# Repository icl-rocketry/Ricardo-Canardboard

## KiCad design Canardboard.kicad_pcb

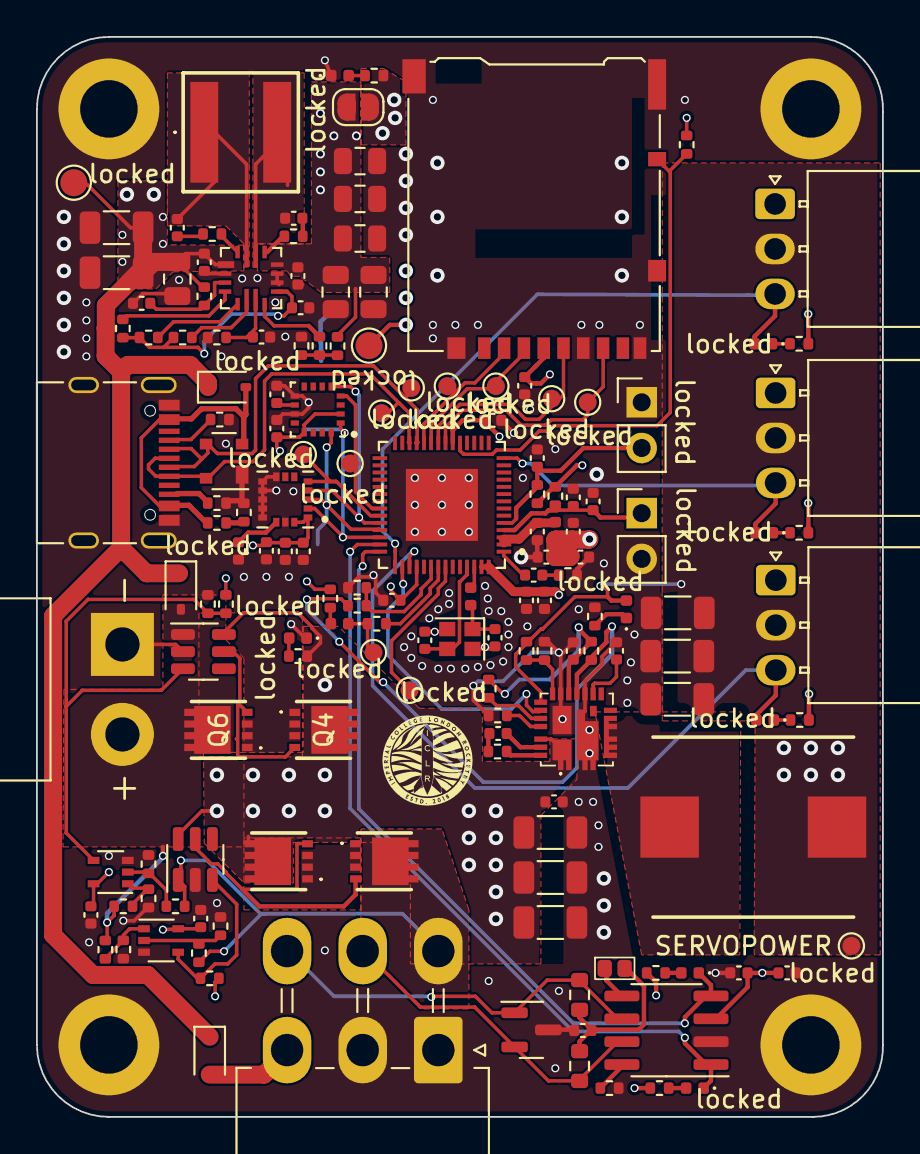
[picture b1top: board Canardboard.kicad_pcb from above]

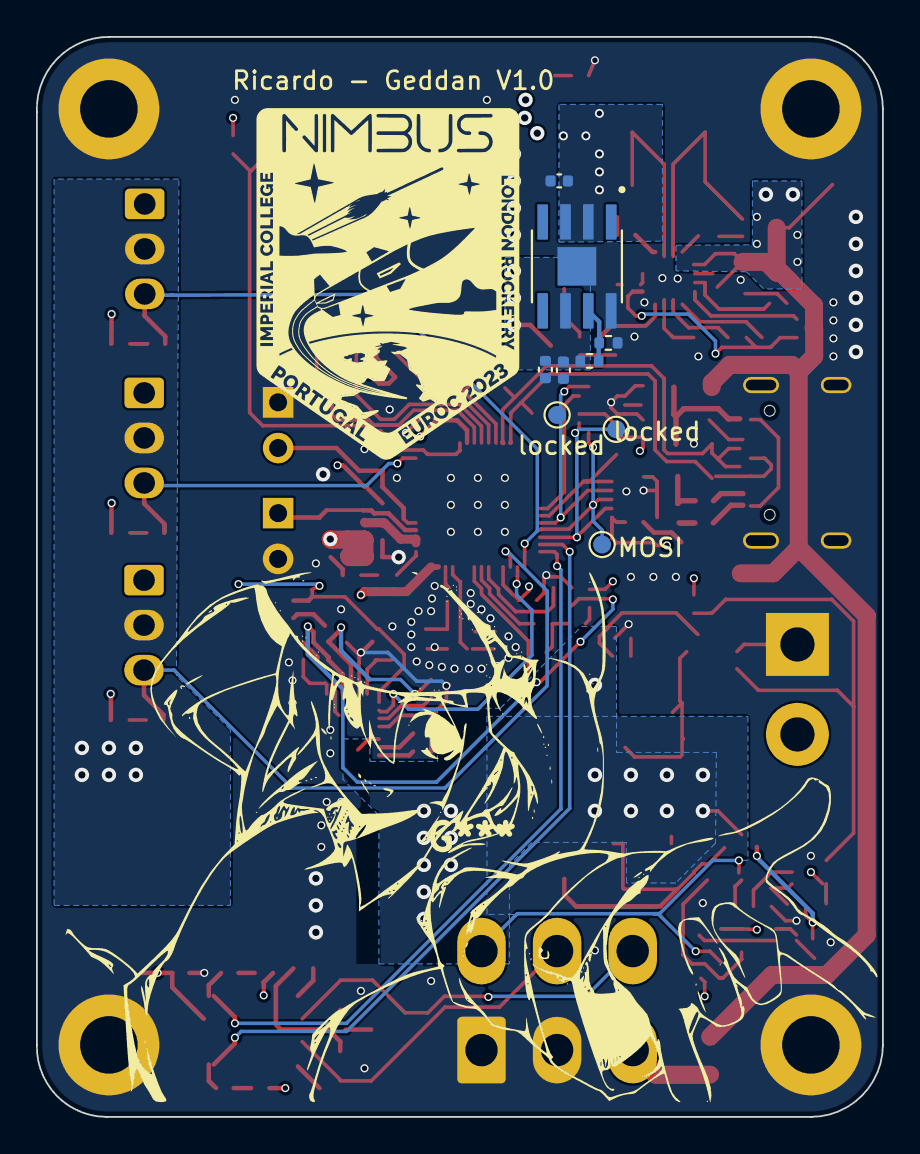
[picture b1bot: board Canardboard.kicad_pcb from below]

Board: 4 copper layers, 47.0 x 60.0 mm, 171 parts (9 on the bottom side), 94 nets.

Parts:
C1, C16, C29: 10uF; C_0402_1005Metric
C2, C4, C7, C20, C22, C23, C32, C42, C52: 1uF; C_0402_1005Metric
C3, C5, C6, C8, C10, C11, C26, C33, C44: 0.1uF; C_0402_1005Metric
C9, C31: 10nF; C_0402_1005Metric
C12: 4.2pF; C_0402_1005Metric
C13, C14: C; C_0402_1005Metric
C15, C40, C41, C49, C53, C54: 100nF; C_0402_1005Metric
C17: 47nF; C_0402_1005Metric
C18, C19, C35, C36, C37, C39, C45, C46: 47uF; C_1206_3216Metric
C21: 4.7uF; C_0402_1005Metric
C24, C25: DNP; C_0402_1005Metric
C30: 0.47uF; C_0402_1005Metric
C34: 2.2uF; C_0402_1005Metric
C43, C50, C51, C56, C57, C58: 22uF; C_0805_2012Metric
C48, C55: 22nF; C_0402_1005Metric
D1: SM712_SOT23; SOT-23
D2: SP0503BAHT; SOT-143
D3, D4, D5: D_Schottky; D_SOD-323
H1, H2, H3, H4: MountingHole_Pad; MountingHole_3.2mm_M3_DIN965_Pad
IC1: SIC437DED-T1-GE3; SiC437BEDT1GE3
J1: RBUS; Molex_Mini-Fit_Jr_5569-06A2_2x03_P4.20mm_Horizontal
J2: USB_C_Receptacle_USB2.0; USB_C_Receptacle_Palconn_UTC16-G
J3: Micro_SD_Card_Det; microSD_HC_Hirose_DM3AT-SF-PEJM5
J4: Conn_01x02_Male; AMASS_XT30PW-M_1x02_P2.50mm_Horizontal
J5, J6, J7: Conn_01x03_Male; Molex_Nano-Fit_105313-xx03_1x03_P2.50mm_Horizontal
JP1: TermJP; SmallerSolderJP
JP2: TermJP; SolderJumper-2_P1.3mm_Open_RoundedPad1.0x1.5mm
L1: 2.0nH; L_0402_1005Metric
L2: 20nH; L_0402_1005Metric
L4: 2.1uH; INDPM112100X400N
L5: 4.7uH; MPLAL60504R7
MOSI: TestPoint; TestPoint_Pad_D1.0mm
Q1, Q2, Q4, Q6: PXP012-30QLJ; PXP01230QLJ
R1, R3: 10K; R_0402_1005Metric
R2, R4, R13, R15, R42, R44, R46: 470; R_0402_1005Metric
R5: 47.5; R_0402_1005Metric
R6: 499; R_0402_1005Metric
R7, R22: 3k; R_0402_1005Metric
R8, R36, R37, R49: 0; R_0402_1005Metric
R9, R10: 60; R_0603_1608Metric
R11, R12: 5.1k; R_0402_1005Metric
R14, R18, R39, R40, R41: 10k; R_0402_1005Metric
R16, R23, R26, R27, R28, R29, R30, R31, R43, R45: 1k; R_0402_1005Metric
R17: 34k; R_0402_1005Metric
R19, R35, R47, R48: 100k; R_0402_1005Metric
R20: 200k; R_0402_1005Metric
R21: 2.2; R_0402_1005Metric
R24: 1.5k; R_0402_1005Metric
R25: 2.2k; R_0402_1005Metric
R32: 499k; R_0402_1005Metric
R33: 806k; R_0402_1005Metric
R34: 230k; R_0402_1005Metric
R38: 21.5k; R_0402_1005Metric
R50, R51: DNP; R_0402_1005Metric
SERVOPOWER: TestPoint; TestPoint_Pad_D1.0mm
U1: ESP32-S3; QFN40P700X700X90-57N
U2: SN65HVD230; SOIC-8_3.9x4.9mm_P1.27mm
U3, U4: LTC4412xS6; TSOT-23-6
U5: 74AHC1G00; SOT-353_SC-70-5
U6: 74AHC1G08; SOT-353_SC-70-5
U9: SC4215; SOIC127P599X175-9N
U10: MP28167GQ-A-Z
USBLED1: USB_LED; R_0402_1005Metric
Y1: 40MHz±10ppm; Crystal_SMD_2016-4Pin_2.0x1.6mm
locked: SERVOLED; LED_0402_1005Metric
locked#2, locked#6, locked#7, locked#10, locked#11, locked#15, locked#17, locked#18, locked#21, locked#25, locked#26, locked#27: TestPoint; TestPoint_Pad_D1.0mm
locked#3, locked#24: Conn_01x02_Male; PinHeader_1x02_P2.54mm_Vertical
locked#4: TX_LED; LED_0402_1005Metric
locked#5, locked#16: TestPoint; TestPoint_Pad_D1.5mm
locked#8, locked#19: SERVOLED; LED_0402_1005Metric
locked#9: CANRXLED; LED_0402_1005Metric
locked#12: MMC5983MA; PQFN50P300X300X100-16N
locked#13: ICM-20608-G; PQFN50P300X300X80-16N
locked#14: 3V3LED; LED_0402_1005Metric
locked#20: 12V_LED; LED_0402_1005Metric
locked#22: SERVOPWR_LED; LED_0402_1005Metric
locked#23: CANTXLED; LED_0402_1005Metric

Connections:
+3.3V: C1.1, C4.1, C5.1, C7.1, C9.1, C10.1, C11.1, C15.1, C16.1, C20.2, C22.2, C23.2, C25.2, C26.2, C31.1, C32.1, C33.1, C34.1, J3.4 (VDD), JP2.2 (B), L1.1, R1.1, R2.1, R3.1, R4.2, R14.1, R26.1, R27.1, R47.1, R48.1, R50.1, U1.20 (VDD3P3_RTC), U1.46 (VDD3P3_CPU), U1.55 (VDDA), U1.56 (VDDA), U2.3 (VCC), U5.5 (VCC), U6.5 (VCC), U9.6 (VOUT), locked#12.2 (VDD), locked#12.13 (VDDIO), locked#13.1 (VDDIO), locked#13.16 (VDD), locked#16.1
+12V: C39.2, C40.2, C45.2, C46.2, IC1.1 (VIN_1), IC1.2 (VIN_2), IC1.22 (VIN_3), IC1.26 (VIN_4), Q1.5 (D_1), Q1.6 (D_2), Q1.7 (D_3), Q1.8 (D_4), Q1.9 (D_5), Q4.5 (D_1), Q4.6 (D_2), Q4.7 (D_3), Q4.8 (D_4), Q4.9 (D_5), R7.1, U3.6 (SENSE), U4.6 (SENSE)
/BOOT: C8.1, R3.2, U1.5 (GPIO0/BOOT), locked#3.2
/BuckPGOOD: R24.2, R25.1, U1.48 (MTMS/JTAG/GPIO42)
/CAN+: D1.2 (A2), J1.5, R9.1, U2.7 (CANH)
/CAN-: D1.1 (A1), J1.6, R10.2, U2.6 (CANL)
/CAN-BUS/Vref: JP1.1 (A), U2.5 (Vref)
/CAN_RX: U1.42 (GPIO37), U2.4 (R), locked#9.1 (K)
/CAN_TX: U1.41 (GPIO36), U2.1 (D), locked#23.1 (K)
/CHIP_PU: C2.1, C3.1, R1.2, U1.4 (CHIP_PU/RESET), locked#24.1
/Data+: D2.4 (K), J2.A6 (D+), J2.B6 (D+), U1.26 (GPIO20/USB_D+/ADC2_CH9), locked#11.1
/Data-: D2.3 (K), J2.A7 (D-), J2.B7 (D-), U1.25 (GPIO19/USB_D-/ADC2_CH8), locked#25.1
/IMU_CS: U1.37 (SPICLK_P/GPIO47), locked#13.5 (CS), locked#18.1
/MAG_CS: U1.36 (SPICLK_N/GPIO48), locked#10.1, locked#12.4 (~SPI_CS)
/RXD: U1.50 (U0RXD/PROG/GPIO44), locked#7.1
/SD_CLK: J3.5 (CLK), U1.22 (GPIO16/ADC2_CH5/XTAL_32K_N), locked#6.1
/SD_CS: J3.2 (DAT3/CD), U1.24 (GPIO18/ADC2_CH7/DAC_1), locked#2.1
/SD_DET: J3.10 (DET_A), R14.2, U1.19 (GPIO14/ADC2_CH3)
/SD_MISO: J3.7 (DAT0), U1.21 (GPIO15/ADC2_CH4/XTAL_32K_P), locked#17.1
/SD_MOSI: J3.3 (CMD), U1.23 (GPIO17/ADC2_CH6/DAC_2), locked#21.1
/SERVOBUCK_EN: IC1.19 (EN), U1.44 (MTCK/JTAG/GPIO39)
/SERVO_PWR: C35.1, C36.1, C37.1, IC1.18 (VOUT), J5.2, J6.2, J7.2, L4.1, R17.2, SERVOPOWER.1, locked#22.2 (A)
/SERVO_SGNL1: J5.3, U1.43 (GPIO38), locked.2 (A)
/SERVO_SGNL2: J6.3, U1.14 (GPIO9/ADC1_CH8), locked#19.2 (A)
/SERVO_SGNL3: J7.3, U1.45 (MTDO/JTAG/GPIO40), locked#8.2 (A)
/SPI_CLK: U1.40 (GPIO35), locked#12.1 (SCL/SPI_SCK), locked#13.2 (SCL/SCLK), locked#26.1
/SPI_MISO: U1.38 (GPIO33), locked#12.5 (SPI_SDO), locked#13.4 (AD0/SDO), locked#27.1
/SPI_MOSI: MOSI.1, U1.39 (GPIO34), locked#12.16 (SDA/SPI_SDI), locked#13.3 (SDA/SDI)
/TXD: R6.1, locked#4.1 (K), locked#15.1
/rbusmosfets/BatteryPower: D3.2 (A), J4.2, Q6.5 (D_1), Q6.6 (D_2), Q6.7 (D_3), Q6.8 (D_4), Q6.9 (D_5), R16.1, R43.1, U4.1 (VIN)
/rbusmosfets/RBUS_3.3: D4.2 (A), J1.3
/rbusmosfets/RBUS_DEPL: J1.4, Q2.5 (D_1), Q2.6 (D_2), Q2.7 (D_3), Q2.8 (D_4), Q2.9 (D_5), R23.2, R45.2, U3.1 (VIN)
/servopower/PGOOD: IC1.14 (PGOOD), R18.1, R24.1
/servopower/SW: IC1.5 (SW_1), IC1.6 (SW_2), IC1.7 (SW_3), IC1.8 (SW_4), IC1.9 (SW_5), IC1.30 (SW_6), L4.2
/servopower/VDD: C42.1, IC1.15 (VDD), R18.2, R20.2
/servopower/uC_VCC: C52.1, R39.1, R40.1, R41.1, U10.9 (VCC)
/servopower/uC_VOUT: C24.1, C49.1, C50.1, C51.1, C56.1, C57.1, C58.1, JP2.1 (A), R34.1, U9.2 (EN), U9.3 (VIN), U10.12 (OUT)
GND: C1.2, C2.2, C3.2, C4.2, C5.2, C6.2, C7.2, C8.2, C9.2, C10.2, C11.2, C13.2, C14.2, C15.2, C16.2, C17.2, C18.2, C19.2, C20.1, C21.1, C22.1, C23.1, C24.2, C25.1, C26.1, C29.2, C30.2, C31.2, C32.2, C33.2, C34.2, C35.2, C36.2, C37.2, C39.1, C40.1, C41.2, C42.2, C43.2, C45.1, C46.1, C48.1, C49.2, C50.2, C51.2, C52.2, C55.2, C56.2, C57.2, C58.2, D1.3 (common), D2.1 (A), H1.1, H2.1, H3.1, H4.1, IC1.3 (PGND__1), IC1.4 (PGND__2), IC1.13 (PGND__3), IC1.16 (AGND_1), IC1.25 (AGND_2), IC1.27 (PGND__4), IC1.29 (PGND__5), J1.1, J1.2, J2.A1 (GND), J2.A12 (GND), J2.B1 (GND), J2.B12 (GND), J2.S1 (SHIELD), J3.6 (VSS), J3.9 (DET_B), J3.11 (SHIELD), J4.1, J5.1, J6.1, J7.1, R5.1, R8.2, R11.2, R12.1, R15.2, R19.2, R22.2, R25.2, R28.1, R29.1, R30.1, R31.1, R35.2, R38.1, R42.2, R44.2, R46.2, R49.2, R51.2, U1.57 (GND), U2.2 (GND), U3.2 (GND), U4.2 (GND), U5.3 (GND), U6.3 (GND), U9.8 (GND), U9.9 (GND), U10.2 (GND), U10.10 (AGND), U10.11 (GND), USBLED1.1 (K), Y1.2, Y1.4, locked#3.1, locked#12.9 (GND), locked#12.11 (GND), locked#13.8 (FSYNC), locked#13.9 (GND), locked#13.10 (GND), locked#13.11 (GND), locked#13.12 (GND), locked#13.13 (GND), locked#13.15 (GND), locked#14.1 (K), locked#20.1 (K), locked#24.2
unnamed: R4.1, locked#14.2 (A)
unnamed: R7.2, locked#20.2 (A)
unnamed: C6.1, L1.2, U1.2 (VDD3P3), U1.3 (VDD3P3)
unnamed: C12.1, R5.2
unnamed: C14.1, L2.2, Y1.1
unnamed: C44.1, R21.1
unnamed: C53.1, R36.2
unnamed: C54.1, R37.2
unnamed: R27.2, locked#9.2 (A)
unnamed: R26.2, locked#23.2 (A)
unnamed: C44.2, IC1.23 (BOOT)
unnamed: IC1.17 (FB), R17.1, R22.1
unnamed: IC1.21 (MODE1), R19.1
unnamed: IC1.20 (MODE2), R20.1
unnamed: IC1.24 (PHASE), R21.2
unnamed: C21.2, IC1.12 (VDRV)
unnamed: J2.A5 (CC1), R11.1
unnamed: J2.B5 (CC2), R12.2
unnamed: C17.1, JP1.2 (B), R9.2, R10.1
unnamed: Q1.4 (G), Q2.4 (G), U3.5 (GATE)
unnamed: Q1.1 (S_1), Q1.2 (S_2), Q1.3 (S_3), Q2.1 (S_1), Q2.2 (S_2), Q2.3 (S_3)
unnamed: Q4.4 (G), Q6.4 (G), U4.5 (GATE)
unnamed: Q4.1 (S_1), Q4.2 (S_2), Q4.3 (S_3), Q6.1 (S_1), Q6.2 (S_2), Q6.3 (S_3)
unnamed: R15.1, R16.2, U5.1
unnamed: R23.1, R42.1, U5.2
unnamed: R33.1, R34.2, R35.1
unnamed: R43.2, R44.1, U6.1
unnamed: R45.1, R46.1, U6.2
unnamed: R28.2, locked.1 (K)
unnamed: R29.2, locked#19.1 (K)
unnamed: R30.2, locked#8.1 (K)
unnamed: R31.2, locked#22.1 (K)
unnamed: R2.2, locked#4.2 (A)
unnamed: C12.2, U1.1 (LNA_IN/RF)
unnamed: R6.2, U1.49 (U0TXD/PROG/GPIO43)
unnamed: C13.1, U1.53 (XTAL_N), Y1.3
unnamed: L2.1, U1.54 (XTAL_P)
unnamed: R8.1, U2.8 (Rs)
unnamed: R47.2, U3.3 (CTL), U6.4
unnamed: R48.2, R49.1, U4.3 (CTL), U5.4
unnamed: C30.1, locked#13.14 (REGOUT)
unnamed: C29.1, locked#12.10 (CAP)
unnamed: R50.2, R51.1, U9.7 (ADJ)
unnamed: R39.2, U10.4 (ALT)
unnamed: R37.1, U10.16 (BST1)
unnamed: R36.1, U10.13 (BST2)
unnamed: C48.2, R32.2, U10.3 (EN)
unnamed: R33.2, U10.8 (FB)
unnamed: C55.1, R38.2, U10.7 (OC)
unnamed: R40.2, U10.5 (SCL)
unnamed: R41.2, U10.6 (SDA)
unnamed: C54.2, L5.1, U10.15 (SW1)
unnamed: C53.2, L5.2, U10.14 (SW2)
unnamed: R13.2, USBLED1.2 (A)
RBUS_uC_V: C18.1, C19.1, C41.1, C43.1, D3.1 (K), D4.1 (K), D5.1 (K), R32.1, U10.1 (IN), locked#5.1
VBUS: D2.2 (K), D5.2 (A), J2.A4 (VBUS), J2.A9 (VBUS), J2.B4 (VBUS), J2.B9 (VBUS), R13.1

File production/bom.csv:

Designator,Footprint,Quantity,Value,LCSC Part #
12V,402,1,12V_LED,
3V3_2,402,1,3V3LED,
"3V3, RuCV",TestPoint_Pad_D1.5mm,2,TestPoint,
"BOOT, EN",PinHeader_1x02_P2.54mm_Vertical,2,Conn_01x02_Male,
"C1, C16, C29",402,3,10uF,
"C10, C11, C26, C3, C33, C44, C5, C6, C8",402,9,0.1uF,
C12,402,1,4.2pF,
"C13, C14",402,2,11pF,
"C15, C40, C41, C49, C53, C54",402,6,100nF,
C17,402,1,47nF,
,,,,
"C35, C36, C37",1206,3,47uF,
"C2, C20, C22, C23, C32, C4, C42, C52, C7",402,9,1uF,
C21,402,1,4.7uF,
"C24, C25, R50, R51",402,4,DNP,
C30,402,1,0.47uF,
"C31, C9",402,2,10nF,
C34,402,1,2.2uF,
"C43, C50, C51, C56, C57, C58",805,6,22uF,
"C48, C55",402,2,22nF,
"CLK_2, CLK, CS, D+, D-, ICS, IO, MCS, MISO, MOSI, OI, RX, SERVOPOWER, TX",TestPoint_Pad_D1.0mm,14,TestPoint,
CRX,402,1,CANRXLED,
CTX,402,1,CANTXLED,
D1,SOT-23,1,SM712_SOT23,
D2,SOT-143,1,SP0503BAHT,
"D3, D4, D5",D_SOD-323,3,D_Schottky,
"H1, H2, H3, H4",MountingHole_3.2mm_M3_DIN965_Pad,4,MountingHole_Pad,
IC1,SiC437BEDT1GE3,1,SIC437AED-T1-GE3,
IMU,PQFN50P300X300X80-16N,1,ICM-20608-G,
J1,Molex_Mini-Fit_Jr_5569-06A2_2x03_P4.20mm_Horizontal,1,RBUS,
J2,USB_C_Receptacle_Palconn_UTC16-G,1,USB_C_Receptacle_USB2.0,
J3,microSD_HC_Hirose_DM3AT-SF-PEJM5,1,Micro_SD_Card_Det,
J4,AMASS_XT30PW-M_1x02_P2.50mm_Horizontal,1,Conn_01x02_Male,
"J5, J6, J7",Molex_Nano-Fit_105313-xx03_1x03_P2.50mm_Horizontal,3,Conn_01x03_Male,
JP1,SmallerSolderJP,1,TermJP,
JP2,SolderJumper-2_P1.3mm_Open_RoundedPad1.0x1.5mm,1,TermJP,
L1,402,1,2.0nH,
L2,402,1,20nH,
L4,INDPM112100X400N,1,2.1uH,
L5,MPLAL60504R7,1,4.7uH,
MAG,PQFN50P300X300X100-16N,1,MMC5983MA,
,,,,
"R1, R14, R18, R3, R39, R40, R41",402,7,10K,
"R10, R9",603,2,60,
"R11, R12",402,2,5.1k,
"R13, R15, R2, R4, R42, R44, R46",402,7,470,
"R16, R23, R26, R27, R28, R29, R30, R31, R43, R45",402,10,1k,
R17,402,1,34k,
"R19, R35, R47, R48",402,4,100k,
R20,402,1,200k,
R21,402,1,2.2,
"R22, R7",402,2,3k,
R24,402,1,1.5k,
R25,402,1,2.2k,
R32,402,1,499k,
R33,402,1,806k,
R34,402,1,230k,
"R36, R37, R49, R8",402,4,0,
R38,402,1,21.5k,
,,,,
R6,402,1,499,
"S1, S2, S3",402,3,SERVOLED,
SP,402,1,SERVOPWR_LED,
TXLED,402,1,TX_LED,
,,,,
U10,MP28167GQ-A-Z,1,MP28167GQ-A-Z,
U2,SOIC-8_3.9x4.9mm_P1.27mm,1,SN65HVD230,
"U3, U4",TSOT-23-6,2,LTC4412xS6,
U5,SOT-353_SC-70-5,1,74AHC1G00,
U6,SOT-353_SC-70-5,1,74AHC1G08,
,,,,
USBLED1,402,1,USB_LED,
Y1,Crystal_SMD_2016-4Pin_2.0x1.6mm,1,40MHz±10ppm,

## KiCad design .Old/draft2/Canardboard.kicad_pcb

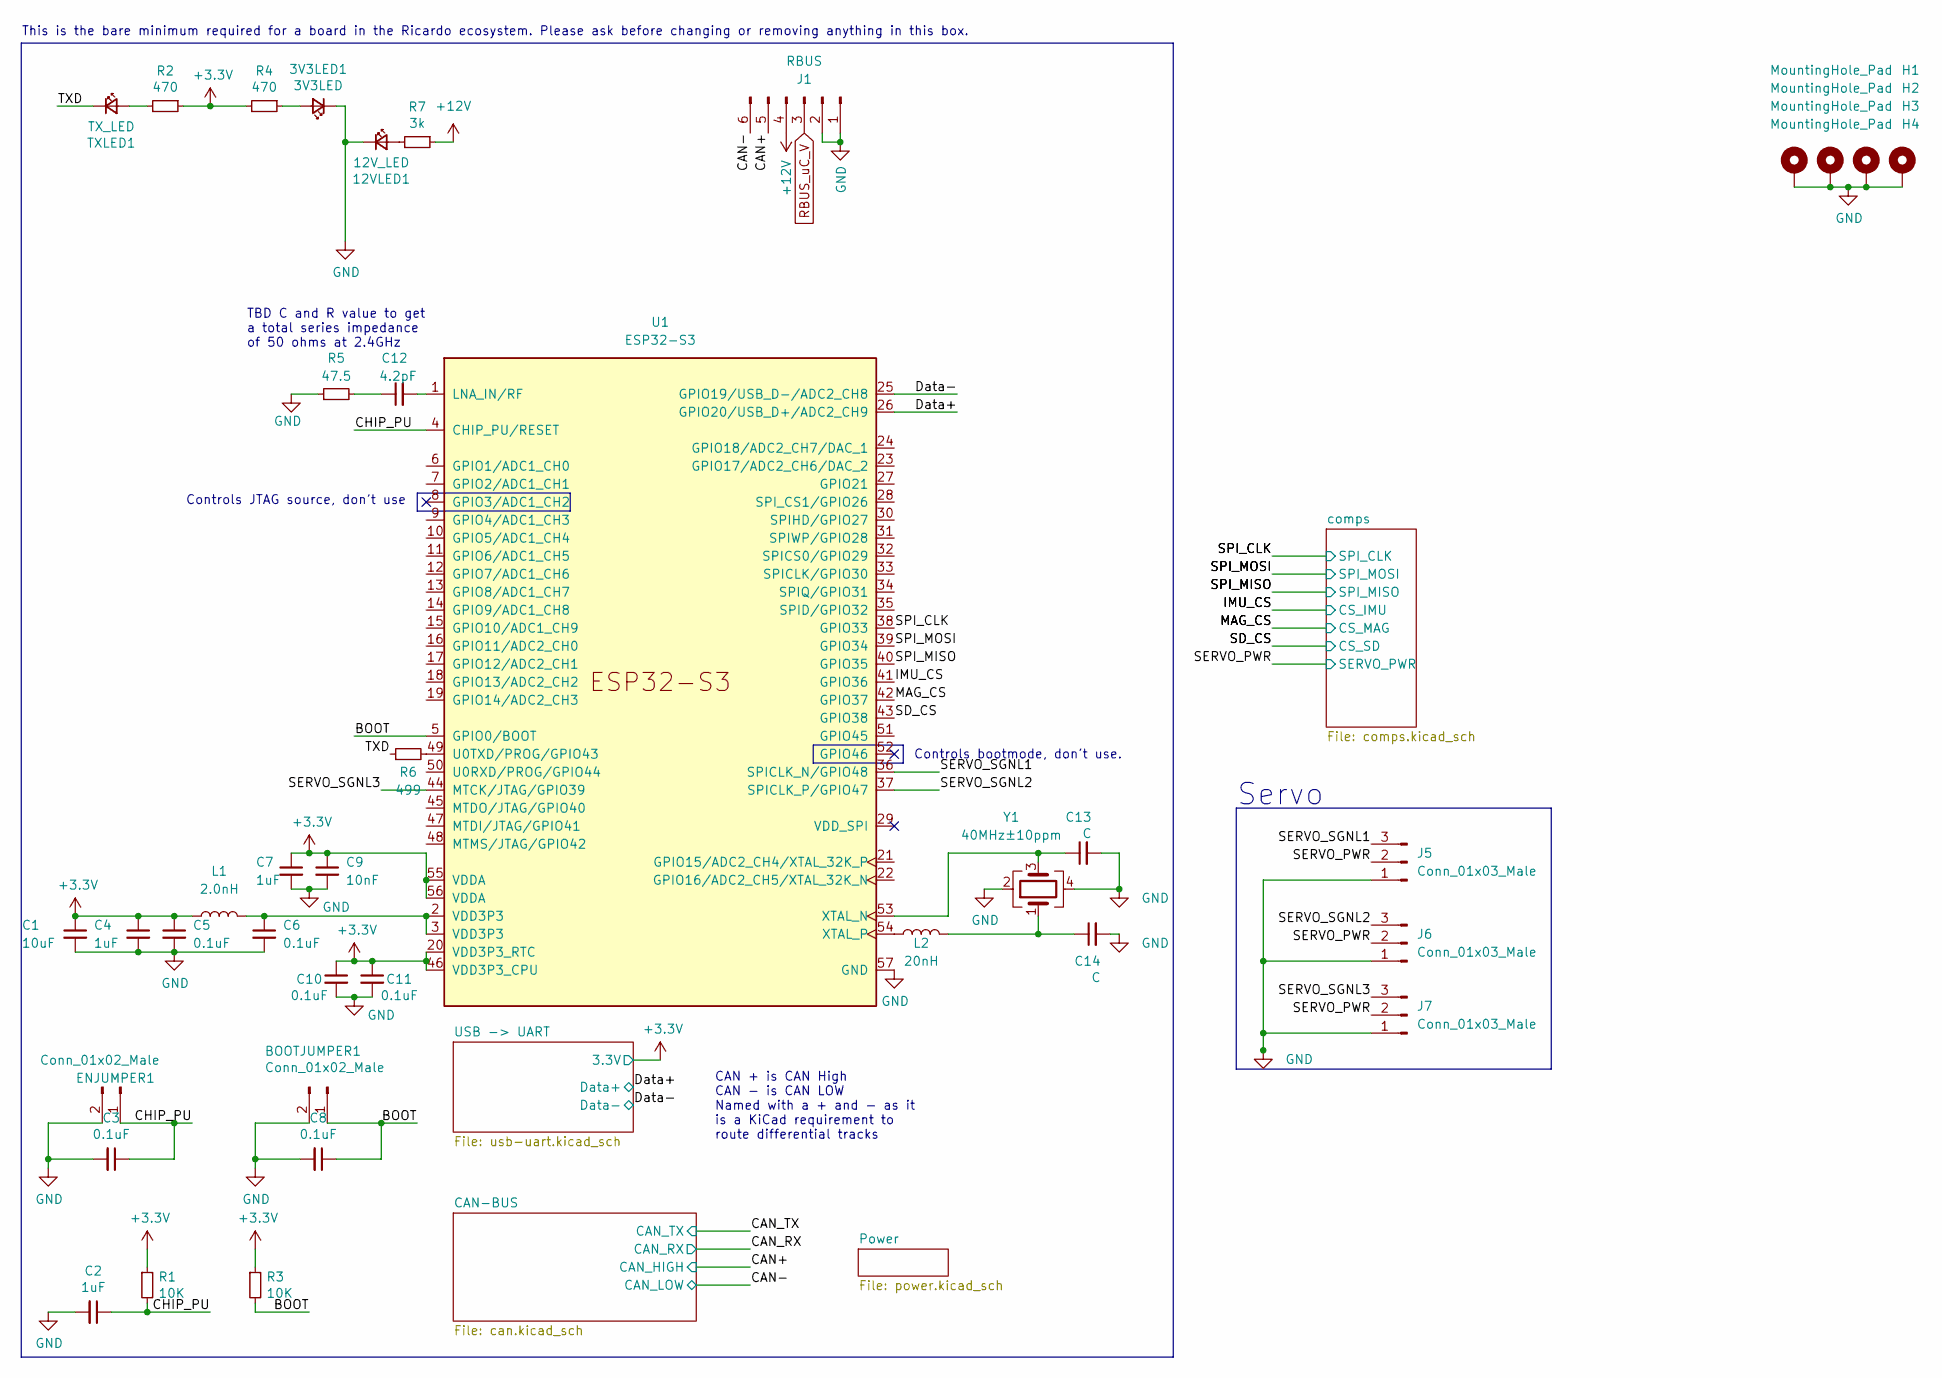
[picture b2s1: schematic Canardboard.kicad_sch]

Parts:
3V3LED1: 3V3LED; R_0402_1005Metric
12VLED1: 12V_LED; R_0402_1005Metric
BOOTJUMPER1: Conn_01x02_Male; PinHeader_1x02_P2.54mm_Vertical
C1: 10uF; C_0402_1005Metric
C2, C4, C7: 1uF; C_0402_1005Metric
C3, C5, C6, C8, C10, C11: 0.1uF; C_0402_1005Metric
C9: 10nF; C_0402_1005Metric
C12: 4.2pF; C_0402_1005Metric
C13, C14: C; C_0402_1005Metric
ENJUMPER1: Conn_01x02_Male; PinHeader_1x02_P2.54mm_Vertical
H1, H2, H3, H4: MountingHole_Pad; MountingHole_3.2mm_M3_DIN965_Pad
J1: RBUS; Molex_Mini-Fit_Jr_5566-06A_2x03_P4.20mm_Vertical
J5, J6, J7: Conn_01x03_Male; AMASS_MR30PW-M_1x03_P3.50mm_Horizontal
L1: 2.0nH; L_0402_1005Metric
L2: 20nH; L_0402_1005Metric
R1, R3: 10K; R_0402_1005Metric
R2, R4: 470; R_0402_1005Metric
R5: 47.5; R_0402_1005Metric
R6: 499; R_0402_1005Metric
R7: 3k; R_0402_1005Metric
TXLED1: TX_LED; R_0402_1005Metric
U1: ESP32-S3; QFN-56-1EP_7x7mm_P0.4mm_EP5.6x5.6mm
Y1: 40MHz±10ppm; Crystal_SMD_2016-4Pin_2.0x1.6mm

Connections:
+3V3: C1.1, C4.1, C5.1, C7.1, C9.1, C10.1, C11.1, L1.1, R1.1, R2.1, R3.1, R4.2, U1.20 (VDD3P3_RTC), U1.46 (VDD3P3_CPU), U1.55 (VDDA), U1.56 (VDDA); also elsewhere on the board
+12V: J1.4, R7.1; also elsewhere on the board
/BOOT: BOOTJUMPER1.1, C8.1, R3.2, U1.5 (GPIO0/BOOT)
/CAN+: J1.5; also elsewhere on the board
/CAN-: J1.6; also elsewhere on the board
/CHIP_PU: C2.1, C3.1, ENJUMPER1.1, R1.2, U1.4 (CHIP_PU/RESET)
/Data+: U1.26 (GPIO20/USB_D+/ADC2_CH9); also elsewhere on the board
/Data-: U1.25 (GPIO19/USB_D-/ADC2_CH8); also elsewhere on the board
/IMU_CS: U1.41 (GPIO36); also elsewhere on the board
/MAG_CS: U1.42 (GPIO37); also elsewhere on the board
/SD_CS: U1.43 (GPIO38); also elsewhere on the board
/SERVO_PWR: J5.2, J6.2, J7.2; also elsewhere on the board
/SERVO_SGNL1: J5.3, U1.36 (SPICLK_N/GPIO48)
/SERVO_SGNL2: J6.3, U1.37 (SPICLK_P/GPIO47)
/SERVO_SGNL3: J7.3, U1.44 (MTCK/JTAG/GPIO39)
/SPI_CLK: U1.38 (GPIO33); also elsewhere on the board
/SPI_MISO: U1.40 (GPIO35); also elsewhere on the board
/SPI_MOSI: U1.39 (GPIO34); also elsewhere on the board
/TXD: R6.1, TXLED1.1 (K)
unnamed: 3V3LED1.2 (A), R4.1
unnamed: 12VLED1.2 (A), R7.2
unnamed: C6.1, L1.2, U1.2 (VDD3P3), U1.3 (VDD3P3)
unnamed: C12.1, R5.2
unnamed: C14.1, L2.2, Y1.1
unnamed: R2.2, TXLED1.2 (A)
unnamed: C12.2, U1.1 (LNA_IN/RF)
unnamed: R6.2, U1.49 (U0TXD/PROG/GPIO43)
unnamed: C13.1, U1.53 (XTAL_N), Y1.3
unnamed: L2.1, U1.54 (XTAL_P)
RBUS_uC_V: J1.3; also elsewhere on the board

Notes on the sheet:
Controls bootmode, don't use.
This is the bare minimum required for a board in the Ricardo ecosystem. Please ask before changing or removing anything in this box.
TBD C and R value to get a total series impedance of 50 ohms at 2.4GHz
CAN + is CAN High CAN - is CAN LOW Named with a + and - as it is a KiCad requirement to route differential tracks
Controls JTAG source, don't use
Servo

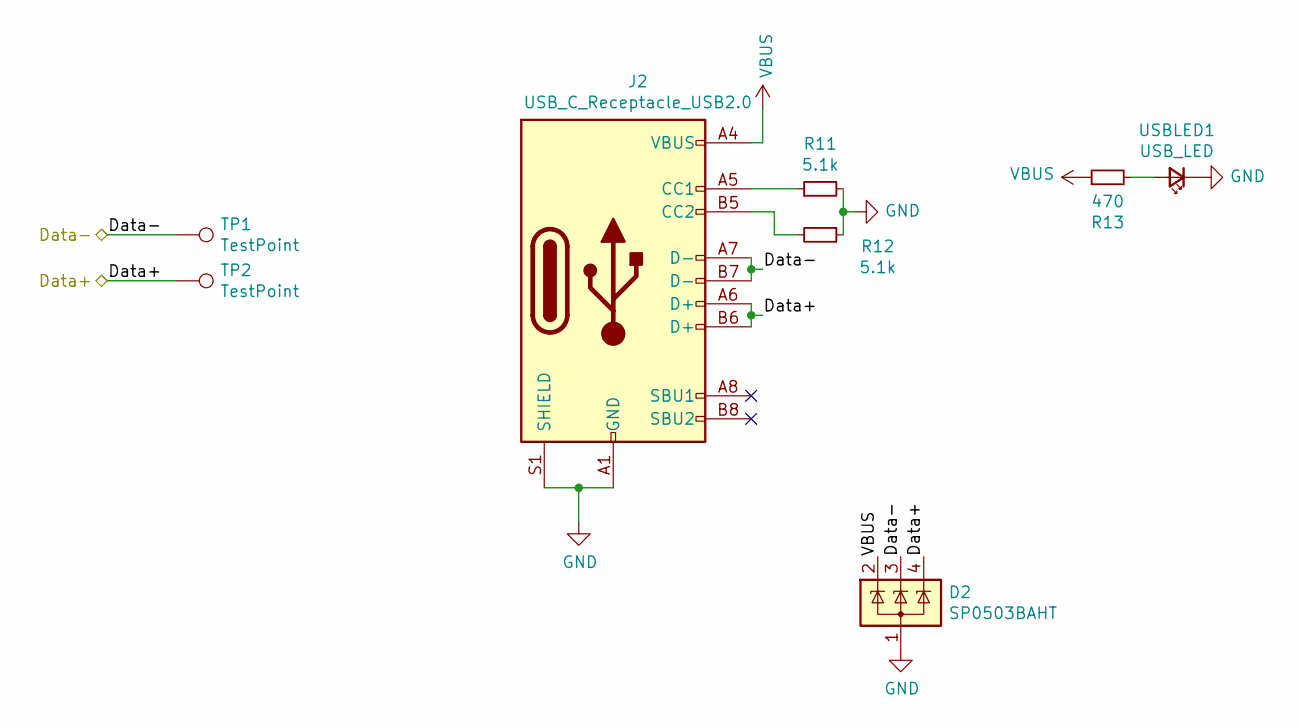
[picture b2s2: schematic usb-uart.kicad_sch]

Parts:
D2: SP0503BAHT; SOT-143
J2: USB_C_Receptacle_USB2.0; USB_C_Receptacle_Palconn_UTC16-G
R11, R12: 5.1k; R_0402_1005Metric
R13: 470; R_0402_1005Metric
TP1, TP2: TestPoint; TestPoint_Pad_D1.0mm
USBLED1: USB_LED; R_0402_1005Metric

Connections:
/Data+: D2.4 (K), J2.A6 (D+), J2.B6 (D+), TP2.1; also elsewhere on the board
/Data-: D2.3 (K), J2.A7 (D-), J2.B7 (D-), TP1.1; also elsewhere on the board
unnamed: J2.A5 (CC1), R11.1
unnamed: J2.B5 (CC2), R12.2
unnamed: R13.2, USBLED1.2 (A)
VBUS: D2.2 (K), J2.A4 (VBUS), J2.A9 (VBUS), J2.B4 (VBUS), J2.B9 (VBUS), R13.1; also elsewhere on the board

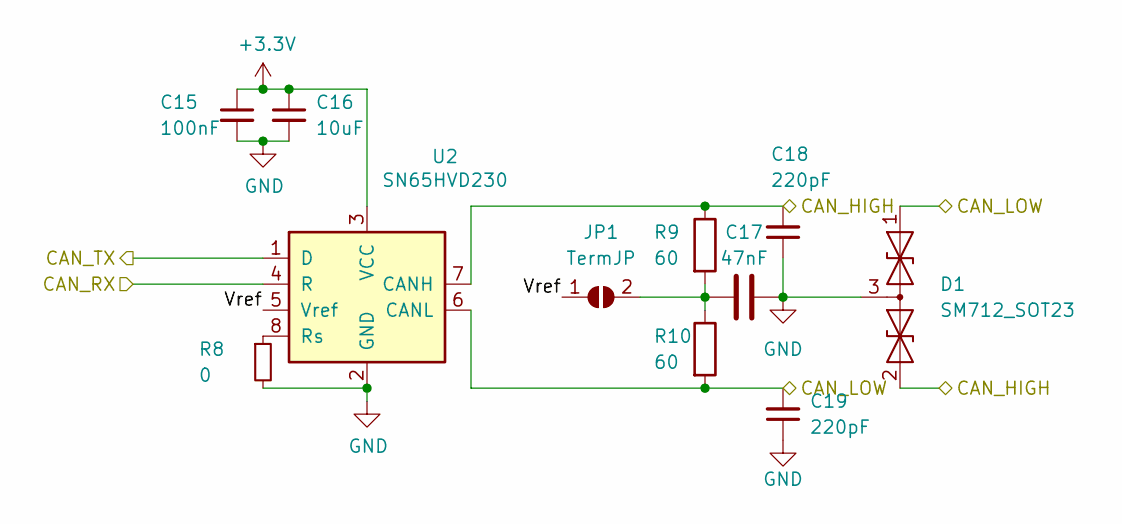
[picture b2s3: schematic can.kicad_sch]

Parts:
C15: 100nF; C_0402_1005Metric
C16: 10uF; C_0402_1005Metric
C17: 47nF; C_0402_1005Metric
C18, C19: 220pF; C_0402_1005Metric
D1: SM712_SOT23; SOT-23
JP1: TermJP; SolderJumper-2_P1.3mm_Open_RoundedPad1.0x1.5mm
R8: 0; R_0603_1608Metric
R9, R10: 60; R_0603_1608Metric
U2: SN65HVD230; SOIC-8_3.9x4.9mm_P1.27mm

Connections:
+3V3: C15.1, C16.1, U2.3 (VCC); also elsewhere on the board
/CAN+: C18.2, D1.2 (A2), R9.1, U2.7 (CANH); also elsewhere on the board
/CAN-: C19.2, D1.1 (A1), R10.2, U2.6 (CANL); also elsewhere on the board
/CAN-BUS/Vref: JP1.1 (A), U2.5 (Vref)
/CAN_RX: U2.4 (R)
/CAN_TX: U2.1 (D)
unnamed: C17.1, JP1.2 (B), R9.2, R10.1
unnamed: R8.1, U2.8 (Rs)

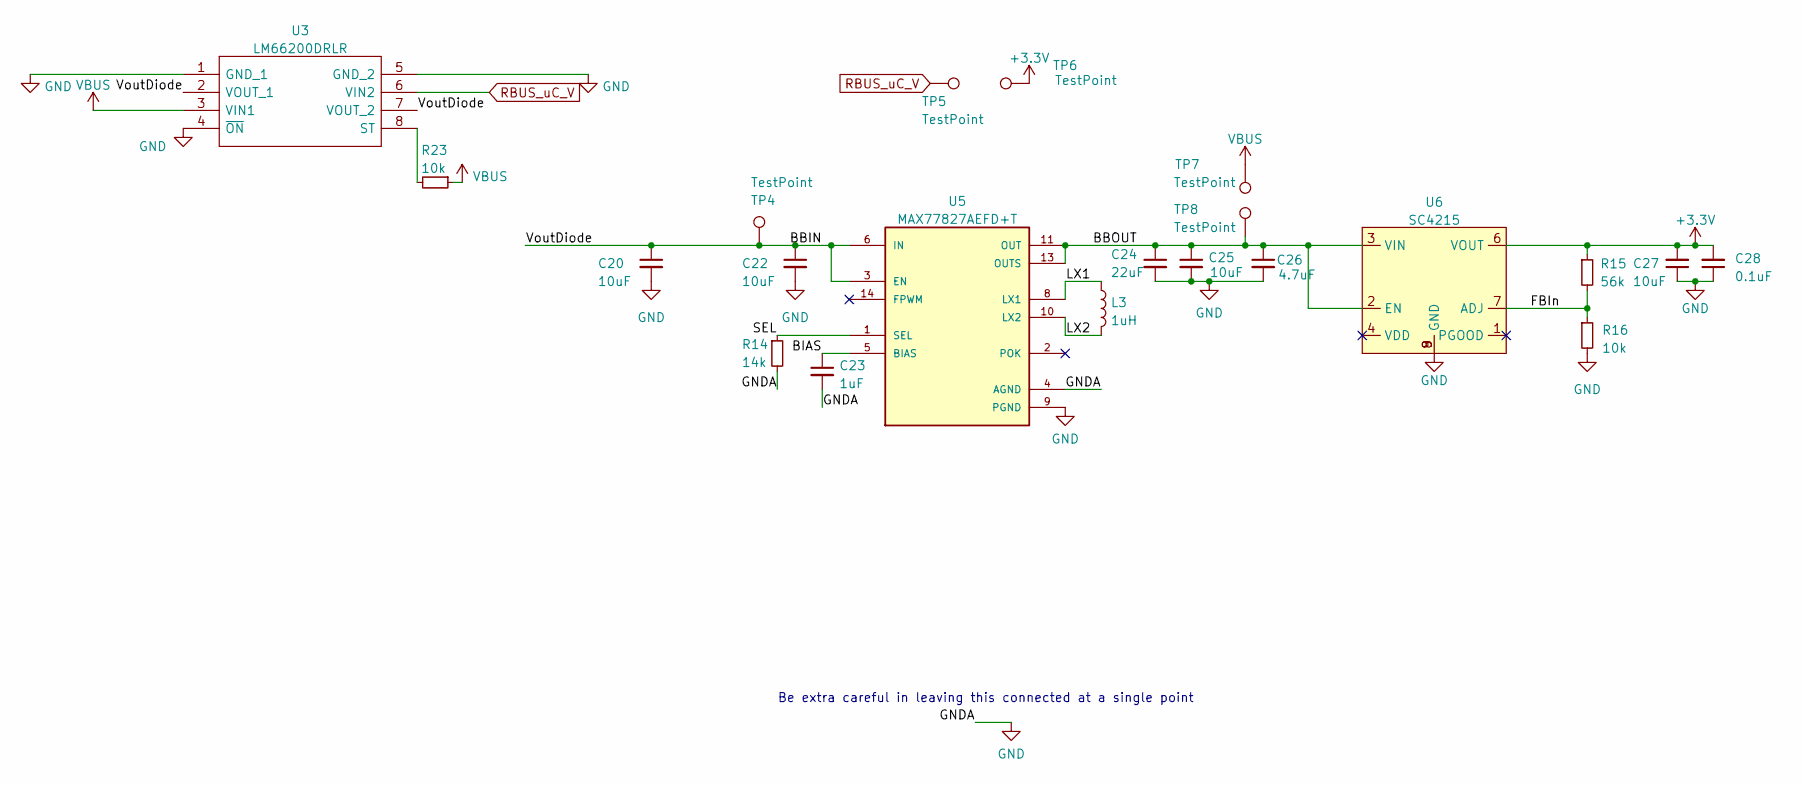
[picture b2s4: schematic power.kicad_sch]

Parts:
C20, C25, C27: 10uF; C_0402_1005Metric
C22: 10uF; C_0603_1608Metric
C23: 1uF; C_0402_1005Metric
C24: 22uF; C_0603_1608Metric
C26: 4.7uF; C_0402_1005Metric
C28: 0.1uF; C_0402_1005Metric
L3: 1uH; L_0805_2012Metric
R14: 14k; R_0402_1005Metric
R15: 56k; R_0402_1005Metric
R16, R23: 10k; R_0402_1005Metric
TP4, TP5, TP6, TP7, TP8: TestPoint; TestPoint_Pad_D1.5mm
U3: LM66200DRLR; SOTFL50P160X60-8N; Manufacturer_Part_Number LM66200DRLR; Mouser Part Number 595-LM66200DRLR
U5: MAX77827AEFD+T; CONV_MAX77827AEFD+T; PARTREV B
U6: SC4215; SOIC127P599X175-9N

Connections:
+3V3: C27.2, C28.2, R15.1, TP6.1, U6.6 (VOUT); also elsewhere on the board
/Power/BBIN: C20.1, C22.1, TP4.1, U3.2 (VOUT_1), U3.7 (VOUT_2), U5.3 (EN), U5.6 (IN)
/Power/BBOUT: C24.1, C25.1, C26.1, TP8.1, U5.11 (OUT), U5.13 (OUTS), U6.2 (EN), U6.3 (VIN)
/Power/BIAS: C23.1, U5.5 (BIAS)
/Power/FBIn: R15.2, R16.1, U6.7 (ADJ)
/Power/LX1: L3.1, U5.8 (LX1)
/Power/LX2: L3.2, U5.10 (LX2)
/Power/SEL: R14.1, U5.1 (SEL)
unnamed: R23.2, U3.8 (ST)
RBUS_uC_V: TP5.1, U3.6 (VIN2); also elsewhere on the board
VBUS: R23.1, TP7.1, U3.3 (VIN1); also elsewhere on the board

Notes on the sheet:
Be extra careful in leaving this connected at a single point

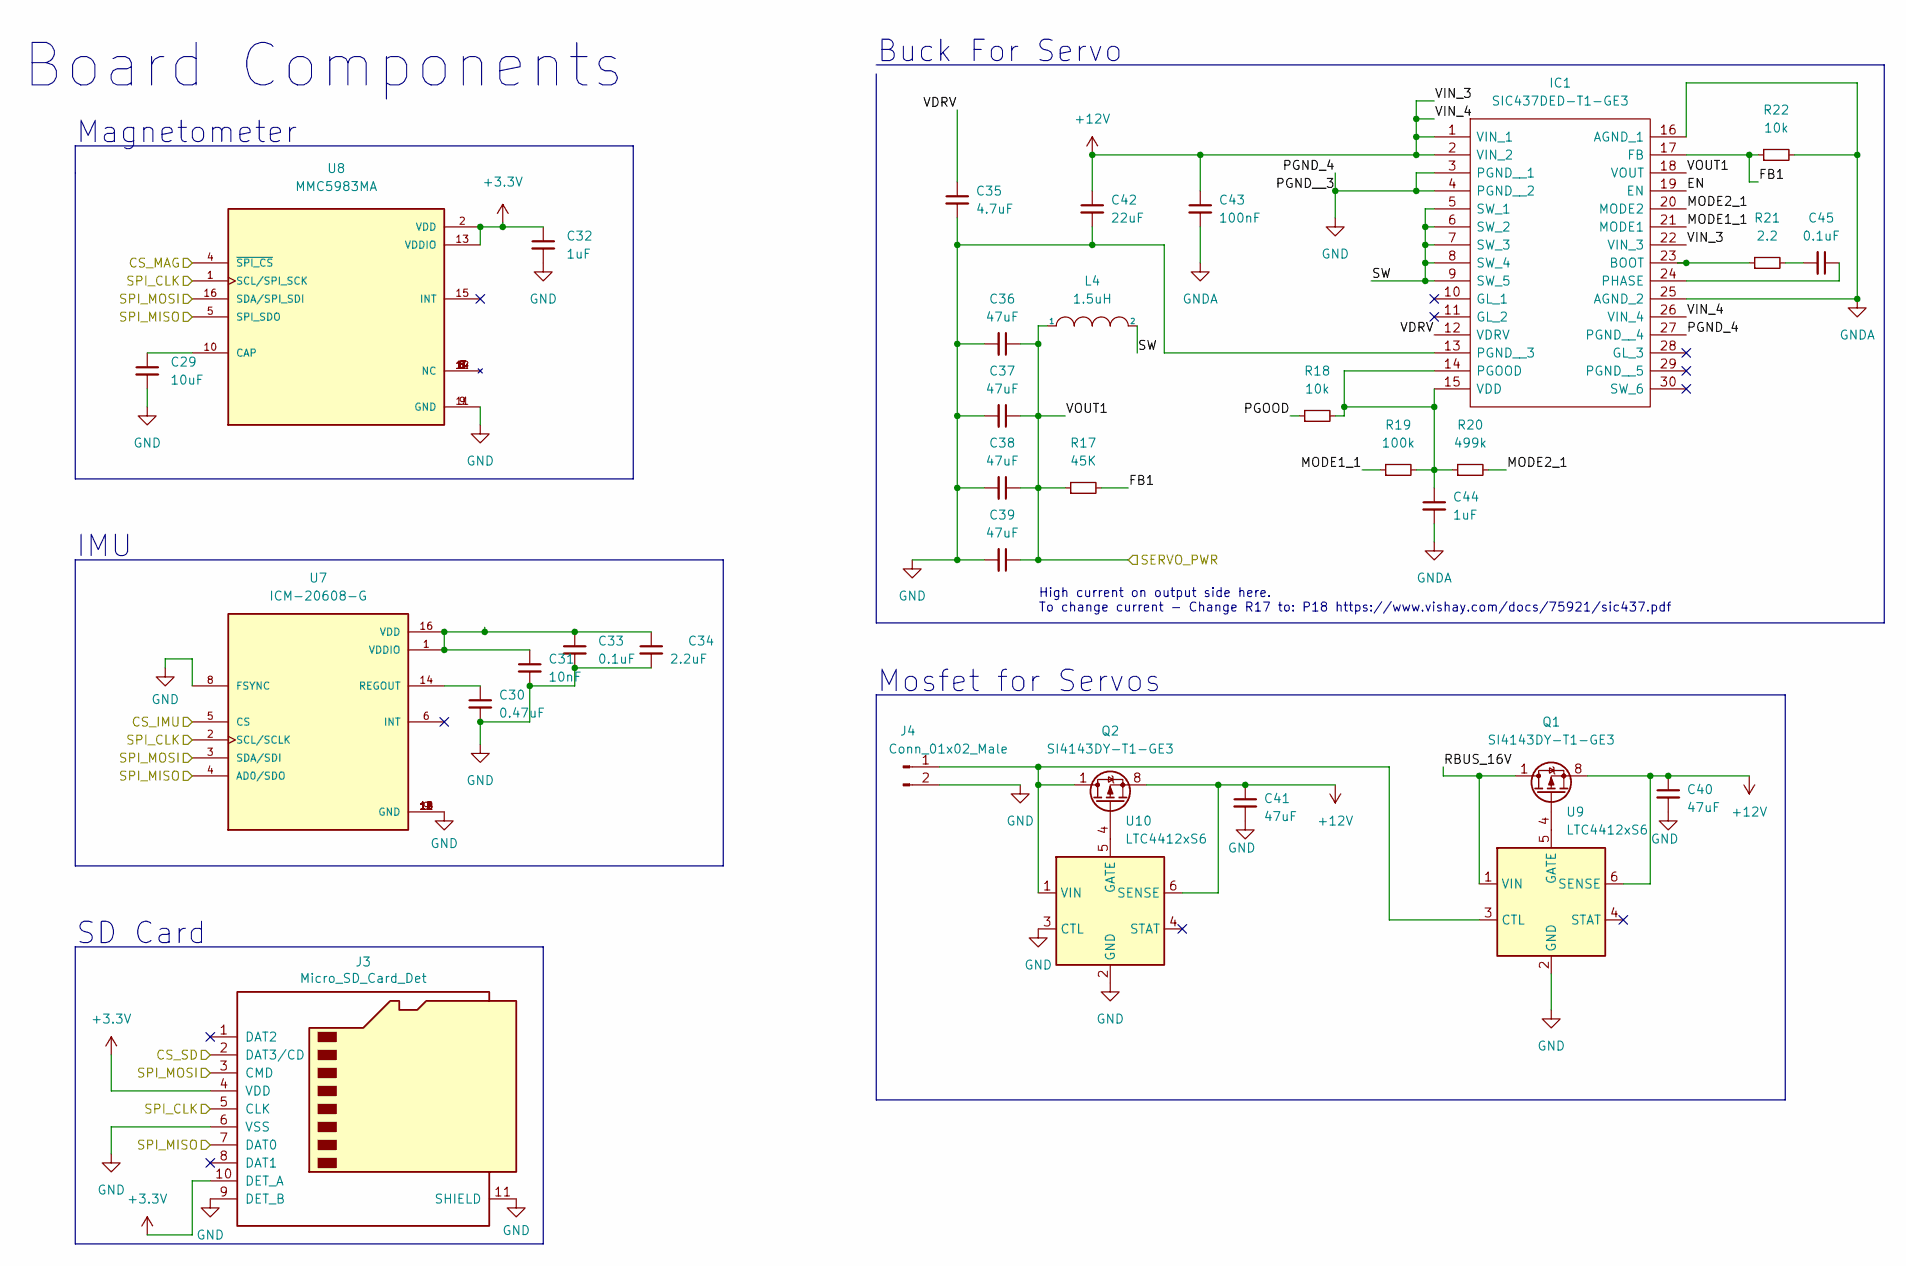
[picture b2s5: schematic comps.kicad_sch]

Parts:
C29: 10uF; C_0603_1608Metric
C30: 0.47uF; C_0603_1608Metric
C31: 10nF; C_0603_1608Metric
C32, C44: 1uF; C_0603_1608Metric
C33, C45: 0.1uF; C_0603_1608Metric
C34: 2.2uF; C_0603_1608Metric
C35: 4.7uF; C_0402_1005Metric
C36, C37, C38, C39: 47uF; C_1206_3216Metric
C40, C41: 47uF; C_0805_2012Metric
C42: 22uF; C_1206_3216Metric
C43: 100nF; C_0805_2012Metric
IC1: SIC437DED-T1-GE3; SIC437DEDT1GE3; Manufacturer_Part_Number SIC437DED-T1-GE3; Mouser Part Number 78-SIC437DED-T1-GE3
J3: Micro_SD_Card_Det; microSD_HC_Hirose_DM3AT-SF-PEJM5
J4: Conn_01x02_Male; AMASS_XT60-M_1x02_P7.20mm_Vertical
L4: 1.5uH; L_1206_3216Metric
Q1, Q2: SI4143DY-T1-GE3; SOIC-8_3.9x4.9mm_P1.27mm
R17: 45K; R_0402_1005Metric
R18, R22: 10k; R_0402_1005Metric
R19: 100k; R_0402_1005Metric
R20: 499k; R_0603_1608Metric
R21: 2.2; R_0603_1608Metric
U7: ICM-20608-G; PQFN50P300X300X80-16N; PARTREV 1.0
U8: MMC5983MA; PQFN50P300X300X100-16N; PARTREV A
U9, U10: LTC4412xS6; TSOT-23-6

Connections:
+3V3: C32.1, J3.4 (VDD), J3.10 (DET_A), U8.2 (VDD), U8.13 (VDDIO); also elsewhere on the board
+12V: C40.1, C41.1, C42.1, C43.1, IC1.1 (VIN_1), IC1.2 (VIN_2), IC1.22 (VIN_3), IC1.26 (VIN_4), Q1.5 (D), Q1.6 (D), Q1.7 (D), Q1.8 (D), Q2.5 (D), Q2.6 (D), Q2.7 (D), Q2.8 (D), U9.6 (SENSE), U10.6 (SENSE); also elsewhere on the board
/IMU_CS: U7.5 (CS); also elsewhere on the board
/MAG_CS: U8.4 (~SPI_CS); also elsewhere on the board
/SD_CS: J3.2 (DAT3/CD); also elsewhere on the board
/SERVO_PWR: C36.1, C37.1, C38.1, C39.1, IC1.18 (VOUT), L4.1, R17.1; also elsewhere on the board
/SPI_CLK: J3.5 (CLK), U7.2 (SCL/SCLK), U8.1 (SCL/SPI_SCK); also elsewhere on the board
/SPI_MISO: J3.7 (DAT0), U7.4 (AD0/SDO), U8.5 (SPI_SDO); also elsewhere on the board
/SPI_MOSI: J3.3 (CMD), U7.3 (SDA/SDI), U8.16 (SDA/SPI_SDI); also elsewhere on the board
/comps/EN: IC1.19 (EN)
/comps/FB1: IC1.17 (FB), R17.2, R22.1
/comps/MODE1_1: IC1.21 (MODE1), R19.1
/comps/MODE2_1: IC1.20 (MODE2), R20.2
/comps/PGOOD: R18.1
/comps/RBUS_16V: Q1.1 (S), Q1.2 (S), Q1.3 (S), U9.1 (VIN)
/comps/SW: IC1.5 (SW_1), IC1.6 (SW_2), IC1.7 (SW_3), IC1.8 (SW_4), IC1.9 (SW_5), L4.2
/comps/VDRV: C35.1, IC1.12 (VDRV)
GNDA: C43.2, C44.2, IC1.16 (AGND_1), IC1.25 (AGND_2), R22.2
unnamed: C45.2, R21.2
unnamed: IC1.23 (BOOT), R21.1
unnamed: C44.1, IC1.14 (PGOOD), IC1.15 (VDD), R18.2, R19.2, R20.1
unnamed: C45.1, IC1.24 (PHASE)
unnamed: Q1.4 (G), U9.5 (GATE)
unnamed: Q2.4 (G), U10.5 (GATE)
unnamed: C30.1, U7.14 (REGOUT)
unnamed: C31.1, C33.1, C34.1, U7.1 (VDDIO), U7.16 (VDD)
unnamed: C29.1, U8.10 (CAP)

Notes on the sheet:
High current on output side here. To change current - Change R17 to: P18 https://www.vishay.com/docs/75921/sic437.pdf
Magnetometer
SD Card
Buck For Servo
Board Components
Mosfet for Servos
IMU

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

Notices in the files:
parts and their libraries:
Copyright 2021 Accelerated Designs. All rights reserved.
